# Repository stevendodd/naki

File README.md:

Project Naki
============

Tracker for a hot-air balloon flight; or other high altitude activity 

Code is written for an ATMega328p microcontroller; and interfaces with http://ukhas.org.uk/ tracking system via radio.  

1. Read GPS and other sensors
2. Create telemetry string containing data
3. Transmit string using RTTY over a Radio transmitter
4. Repeat

###The tracker board has the following features:

* ATMega microcontroller with external 16Mz clock
* Reset jumper to restart the ATMega program
* ublox max7 GPS receiver
* Radiometrix NTX2 radio transmitter - allows license exempt transmitting in the UK
* SMA connector for connecting the radio antenna
* Internal temperature sensor
* External temperature sensor
* Voltage sensor to measure remaining power available
* Socket to connect to a Raspberry Pi 26 pin GPIO header
  * Programming the ATMega directly from the Pi
  * Reading serial output from the ATMega program and logging on the pi SD card
* Power jumpers to allow power from the Raspberry Pi or independent supply
  
###This repository contains the following:

**arduino** - Toolchain installation for a standard Raspberry Pi to compile payload sketch

**docs**	- Instructions and notes (basic)

**eagle** - Eagle schematic and board design

**payload** - Tracker ATMega code/sketch and compile scripts

**scripts** - init.d and logging scripts to save serial output and photos to the Raspberry Pi SD card

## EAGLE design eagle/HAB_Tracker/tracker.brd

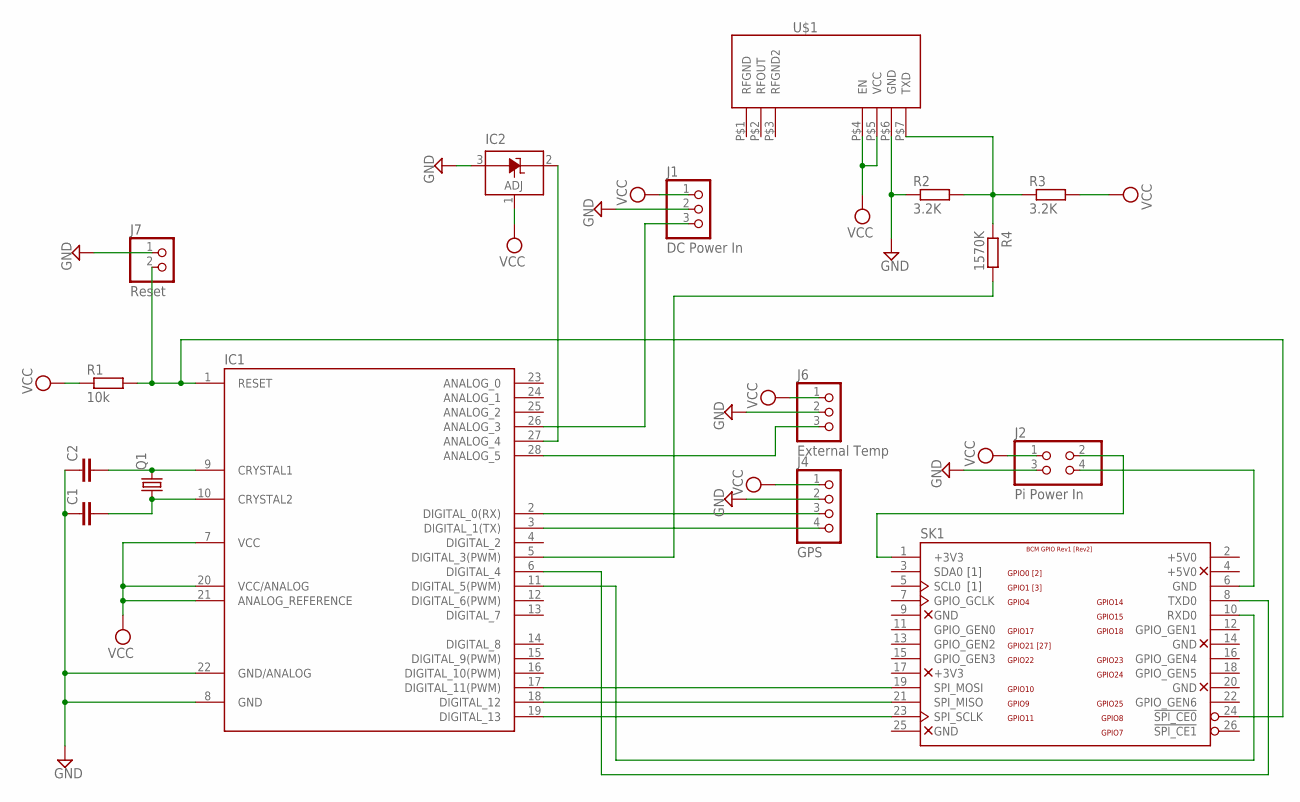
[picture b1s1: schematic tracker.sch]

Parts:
C1, C2: C-EU025-025X050; C025-025X050
IC1: ATMEGA168-PU; DIL28-3
IC2: LM336LP; TO92
J1: DC Power In; 1X03
J2: Pi Power In; 2X02
J4: GPS; 1X04
J6: External Temp; 1X03
J7: Reset; 1X02
Q1: CRYSTALHC49S; HC49/S
R1: 10k; 0207/10
R2, R3: 3.2K; 0207/10
R4: 1570K; 0207/10
SK1: PI-GPIO-PTH; GPIO-CONNECTOR
U$1: NTX2

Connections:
+5V0: SK1.2 (+5V0)
GND: C1.1, C2.1, IC1.8 (GND), IC1.22 (GND/ANALOG), IC2.3 (A), J1.2, J2.3, J4.2, J6.2, J7.1, R2.1, U$1.P$6 (GND)
unnamed: C2.2, IC1.9 (CRYSTAL1), Q1.2
unnamed: C1.2, IC1.10 (CRYSTAL2), Q1.1
unnamed: IC1.2 (DIGITAL_0(RX)), J4.3
unnamed: IC1.11 (DIGITAL_5(PWM)), SK1.10 (RXD0)
unnamed: IC1.1 (RESET), J7.2, R1.2, SK1.24 (!SPI_CE0)
unnamed: IC1.17 (DIGITAL_11(PWM)), SK1.19 (SPI_MOSI)
unnamed: IC1.18 (DIGITAL_12), SK1.21 (SPI_MISO)
unnamed: IC1.19 (DIGITAL_13), SK1.23 (SPI_SCLK)
unnamed: IC1.3 (DIGITAL_1(TX)), J4.4
unnamed: IC1.5 (DIGITAL_3(PWM)), R4.2
unnamed: J2.2, SK1.1 (+3V3)
unnamed: J2.4, SK1.6 (GND)
unnamed: IC1.27 (ANALOG_4), IC2.2 (C)
unnamed: IC1.26 (ANALOG_3), J1.3
unnamed: IC1.28 (ANALOG_5), J6.3
unnamed: R2.2, R3.1, R4.1, U$1.P$7 (TXD)
unnamed: IC1.6 (DIGITAL_4), SK1.8 (TXD0)
VCC: IC1.7 (VCC), IC1.20 (VCC/ANALOG), IC1.21 (ANALOG_REFERENCE), IC2.1 (ADJ), J1.1, J2.1, J4.1, J6.1, R1.1, R3.2, U$1.P$4 (EN), U$1.P$5 (VCC)

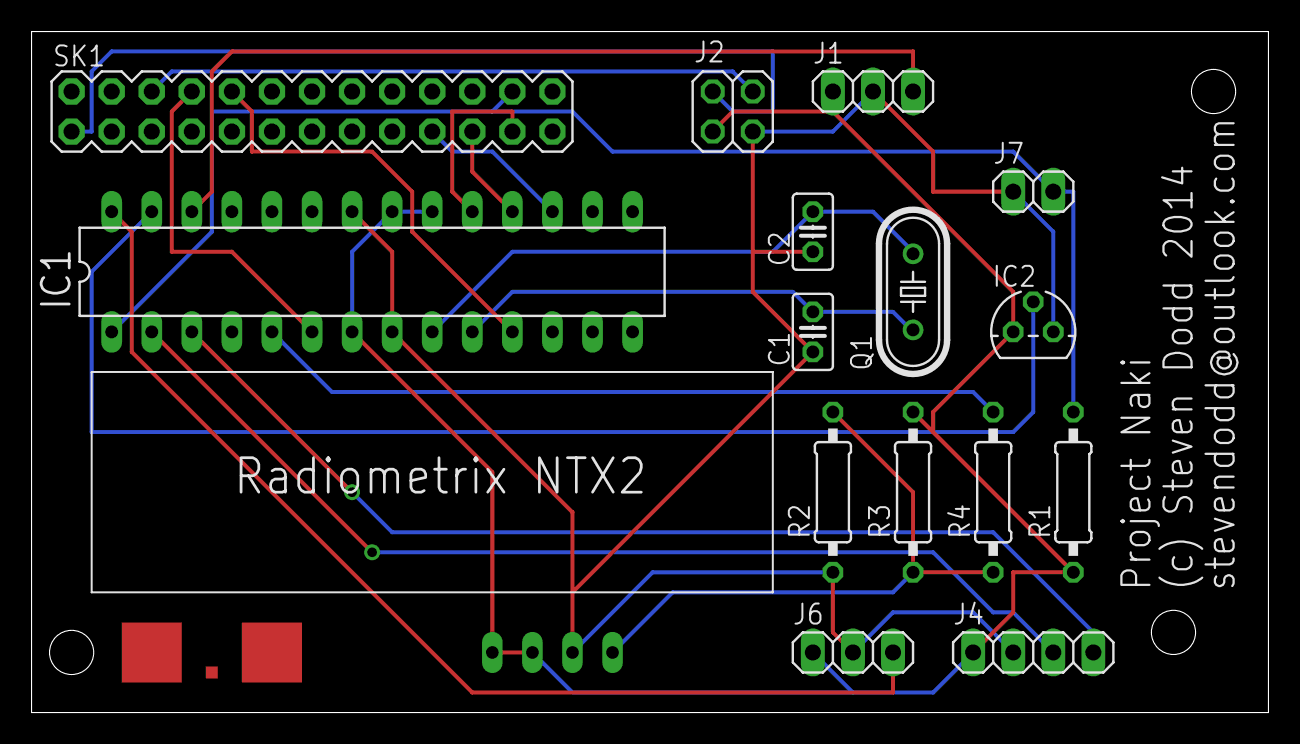
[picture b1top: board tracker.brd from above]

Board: 2 copper layers, 78.4 x 43.2 mm, 16 parts (0 on the bottom side), 19 nets.

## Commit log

2014-08-09 Initial files
2014-08-09 Changed project structure / Added Eagle files
2014-08-09 Added Git Ignore
2014-08-09 Added eagle schematic and board screenshots
2014-08-10 Adding initial arduino toolchain files and docs
2014-08-10 added installer for arduino toolchain setup
2014-08-10 Added Arduino makefiles
2014-08-10 Added config for ATMega328p in avrdude
2014-08-10 Updated install script
2014-08-10 Updated documentation
2014-08-10 Updated readme file with additional information
2014-08-10 Formatted Readme
2014-08-10 Changed digital output pin for the radio transmitter to digital pin 5, this now matches v2 of the tracker board and allows for experimentation of PWM rather than the hardware voltage divider for crea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
2014-08-10 Change to digital pin 3 for radio - not 5...
2014-08-10 fixed newline error
2014-08-18 Added funictionality to readSerial and Added auto start for the readSerial logger
2014-08-18 added photo functionailty
2014-08-19 Renamed scripts to have more meaningful names, added install script
2014-08-24 Added rotating output directory
